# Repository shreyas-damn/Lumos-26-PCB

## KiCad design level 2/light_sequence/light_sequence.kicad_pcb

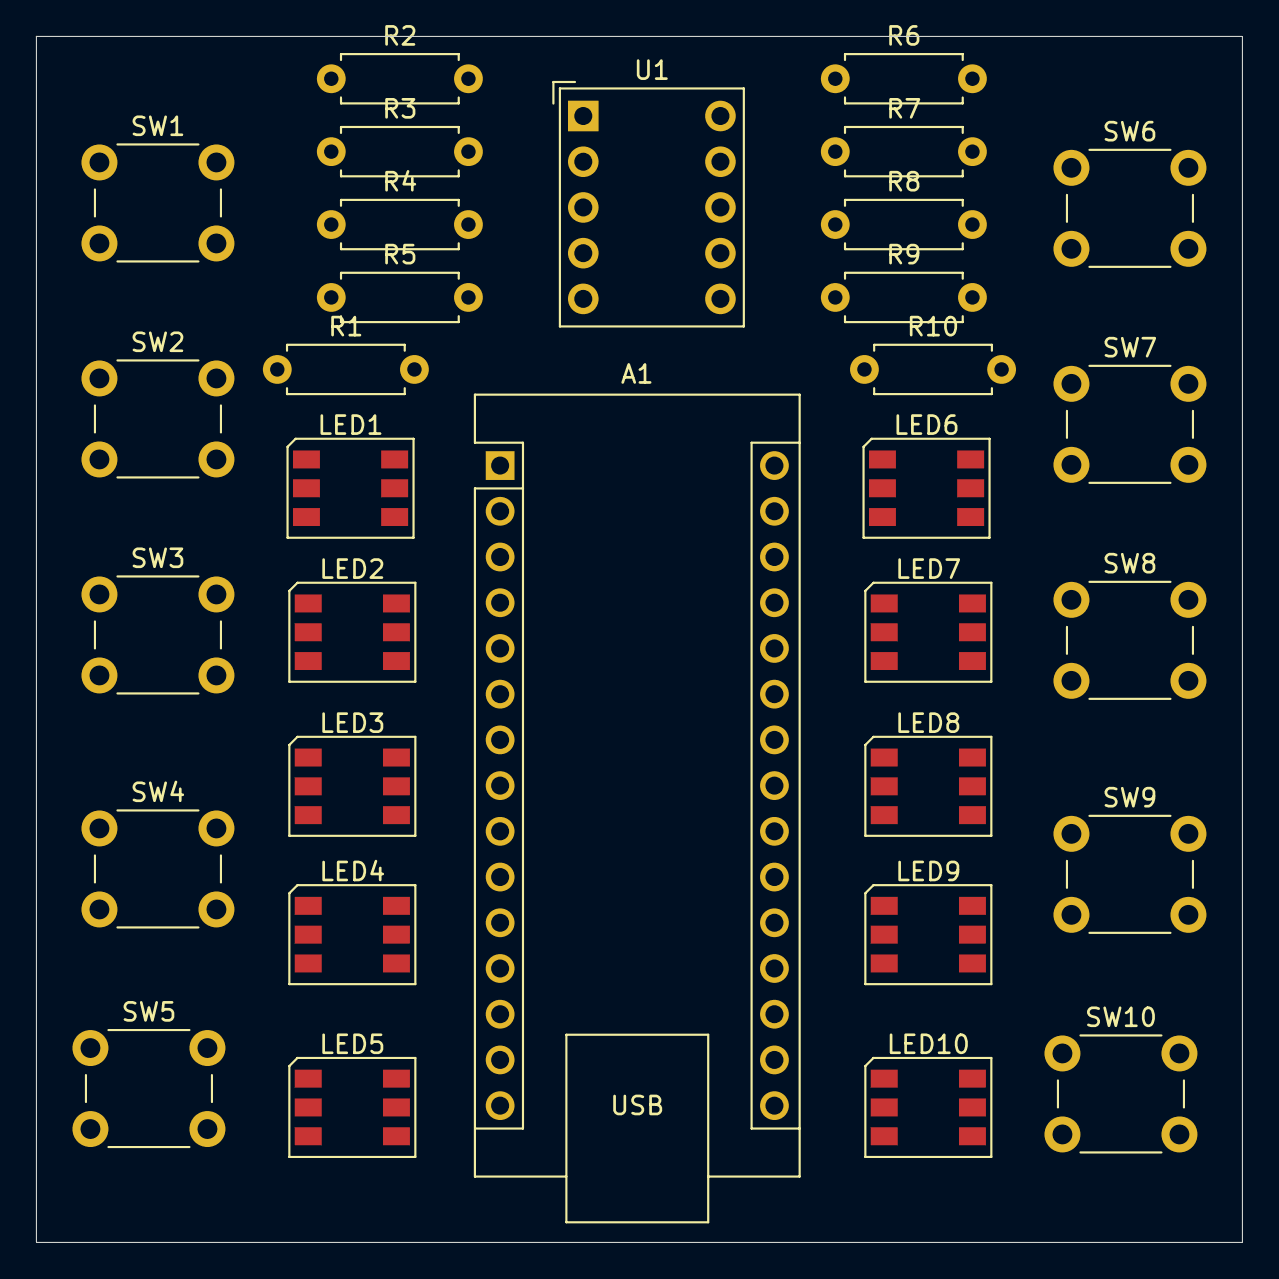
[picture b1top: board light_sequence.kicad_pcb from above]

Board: 2 copper layers, 67.0 x 67.0 mm, 32 parts (0 on the bottom side), 28 nets, no tracks yet.

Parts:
A1: Arduino_Nano_v3.x; Arduino_Nano
LED1, LED2, LED3, LED4, LED5, LED6, LED7, LED8, LED9, LED10: WS2812B; LED_WS2812_PLCC6_5.0x5.0mm_P1.6mm
R1, R10: 470; R_Axial_DIN0207_L6.3mm_D2.5mm_P7.62mm_Horizontal
R2, R3, R4, R5, R6, R7, R8, R9: 220; R_Axial_DIN0207_L6.3mm_D2.5mm_P7.62mm_Horizontal
SW1, SW2, SW3, SW4, SW5, SW6, SW7, SW8, SW9, SW10: SW_Push; SW_PUSH_6mm_H7.3mm
U1: SA39-11SRWA; Sx39-1xxxxx

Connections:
+5V: A1.27 (+5V), U1.3 (CA), U1.8 (CA)
GND: A1.4 (GND), SW1.1, SW2.2, SW3.2, SW4.2, SW5.2, SW6.2, SW7.2, SW8.2, SW9.2, SW10.2
unnamed: A1.19 (A0), SW2.1
unnamed: A1.20 (A1), SW3.1
unnamed: A1.21 (A2), SW4.1
unnamed: A1.22 (A3), SW5.1
unnamed: A1.23 (A4), SW6.1
unnamed: A1.24 (A5), SW7.1
unnamed: A1.25 (A6), SW8.1
unnamed: A1.26 (A7), SW9.1
unnamed: A1.6 (D3), SW10.1
unnamed: A1.8 (D5), SW1.2
unnamed: R2.2, U1.10 (A)
unnamed: R3.2, U1.9 (B)
unnamed: R4.2, U1.7 (C)
unnamed: R5.2, U1.5 (D)
unnamed: R6.2, U1.4 (E)
unnamed: R7.2, U1.2 (F)
unnamed: R8.2, U1.1 (G)
a: A1.10 (D7), R2.1
b: A1.11 (D8), R3.1
c: A1.12 (D9), R4.1
d: A1.13 (D10), R5.1
e: A1.14 (D11), R6.1
f: A1.15 (D12), R7.1
g: A1.16 (D13), R8.1
led_in: A1.9 (D6), R1.1
led_in2: A1.18 (AREF), R10.1

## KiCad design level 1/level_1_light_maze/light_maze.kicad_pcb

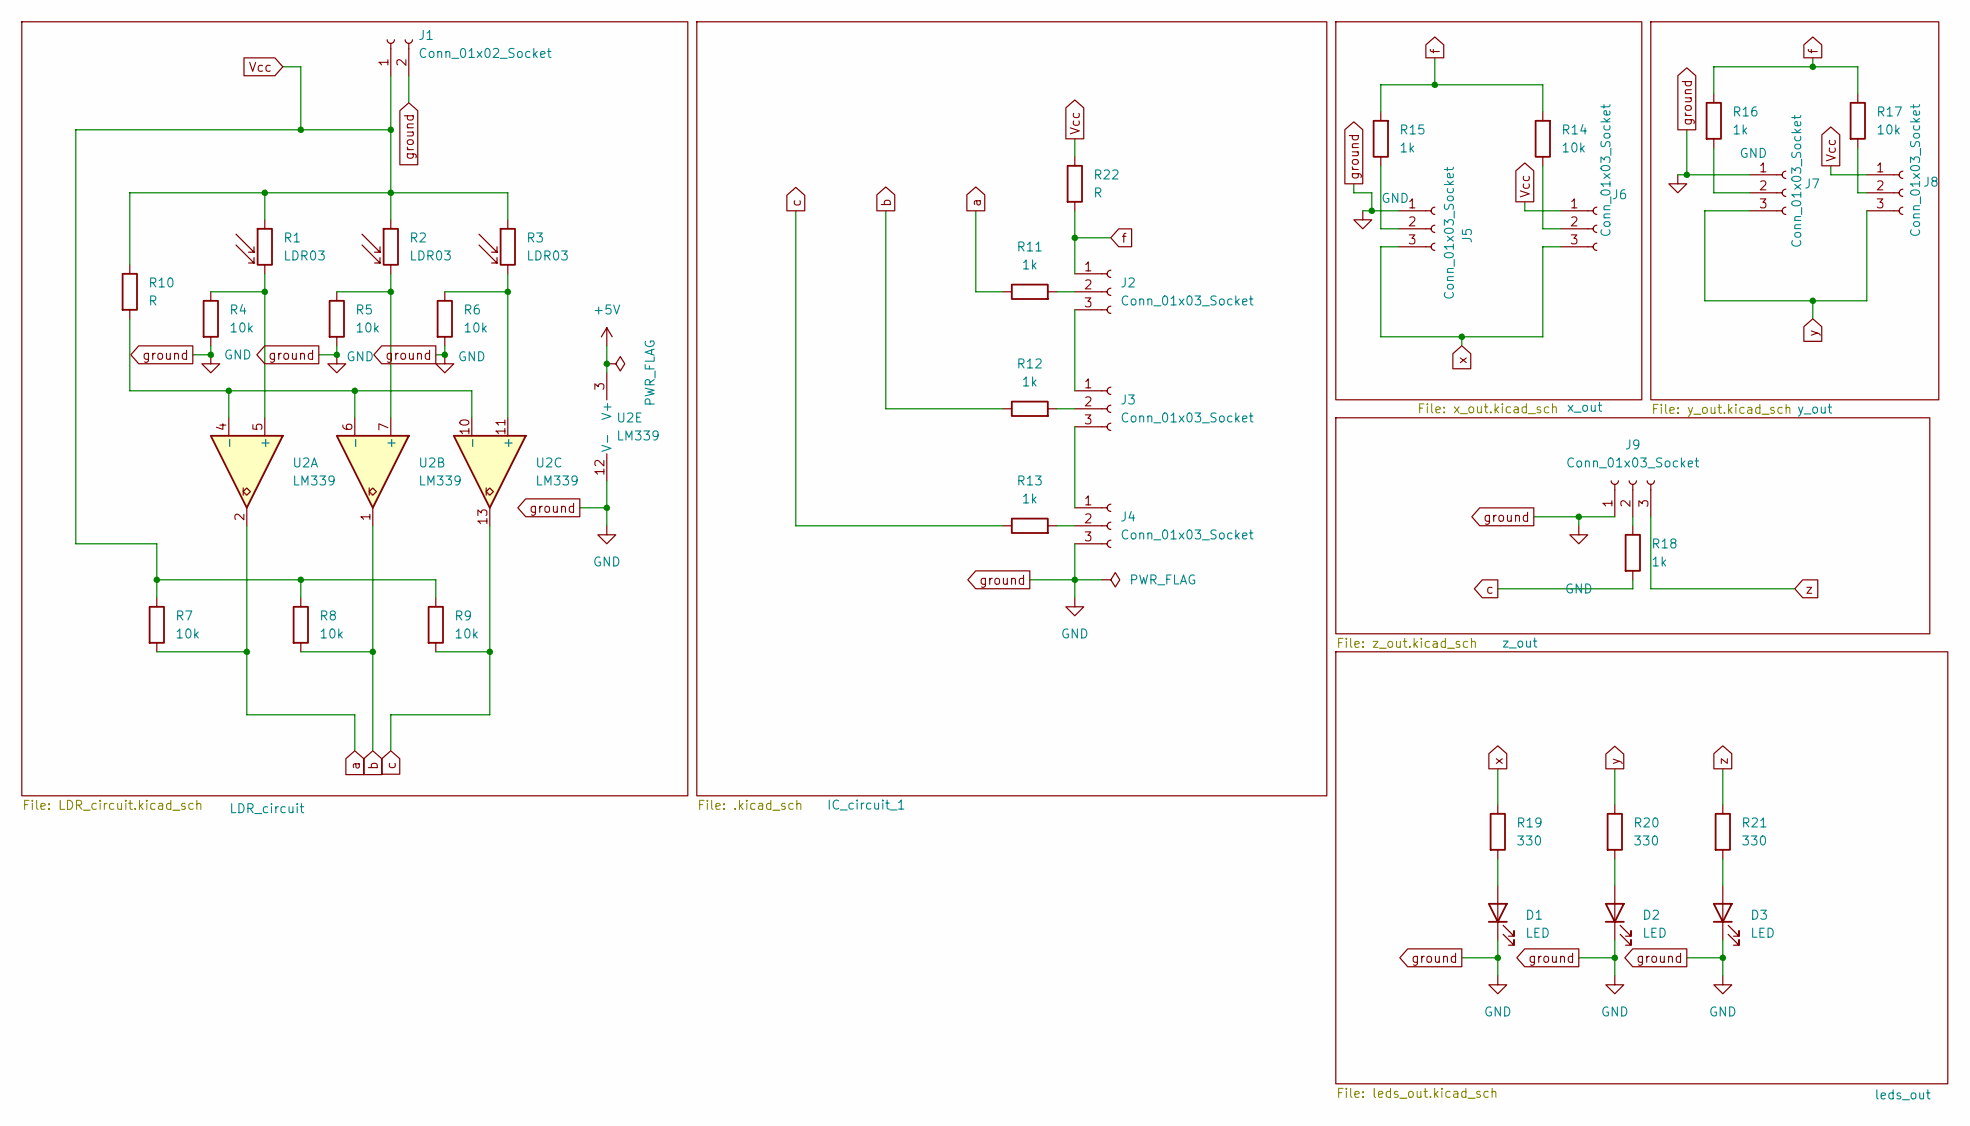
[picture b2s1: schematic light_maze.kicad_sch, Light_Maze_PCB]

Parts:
D1, D2, D3: LED; LED_D3.0mm_Horizontal_O1.27mm_Z2.0mm
J1: Conn_01x02_Socket; PinSocket_1x02_P2.54mm_Vertical
J2, J3, J4, J5, J6, J7, J8, J9: Conn_01x03_Socket; PinSocket_1x03_P2.54mm_Vertical
R1, R2, R3: LDR03; R_LDR_10x8.5mm_P7.6mm_Vertical
R4, R5, R6, R7, R8, R9, R14, R17: 10k; R_Axial_DIN0204_L3.6mm_D1.6mm_P5.08mm_Horizontal
R10, R22: R; R_Axial_DIN0204_L3.6mm_D1.6mm_P5.08mm_Horizontal
R11, R12, R13, R15, R16, R18: 1k; R_Axial_DIN0204_L3.6mm_D1.6mm_P5.08mm_Horizontal
R19, R20, R21: 330; R_Axial_DIN0204_L3.6mm_D1.6mm_P5.08mm_Horizontal
U2: LM339; SOIC-14_3.9x8.7mm_P1.27mm

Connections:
+5V: U2.3 (V+)
unnamed: D1.2 (A), R19.2
unnamed: D2.2 (A), R20.2
unnamed: D3.2 (A), R21.2
unnamed: J2.2, R11.2
unnamed: J2.3, J3.1
unnamed: J3.2, R12.2
unnamed: J3.3, J4.1
unnamed: J4.2, R13.2
unnamed: J5.2, R15.1
unnamed: J6.2, R14.1
unnamed: J7.2, R16.2
unnamed: J8.2, R17.2
unnamed: J9.2, R18.1
unnamed: R1.2, R4.1, U2.5 (+)
unnamed: R10.2, U2.4 (-), U2.6 (-), U2.10 (-)
unnamed: R2.2, R5.1, U2.7 (+)
unnamed: R3.2, R6.1, U2.11 (+)
Vcc: J1.1, J6.1, J8.1, R1.1, R2.1, R3.1, R7.1, R8.1, R9.1, R10.1, R22.1
a: R7.2, R11.1, U2.2
b: R8.2, R12.1, U2.1
c: R9.2, R13.1, R18.2, U2.13
f: J2.1, R14.2, R15.2, R16.1, R17.1, R22.2
ground: D1.1 (K), D2.1 (K), D3.1 (K), J1.2, J4.3, J5.1, J7.1, J9.1, R4.2, R5.2, R6.2, U2.12 (V-)
x: J5.3, J6.3, R19.1
y: J7.3, J8.3, R20.1
z: J9.3, R21.1

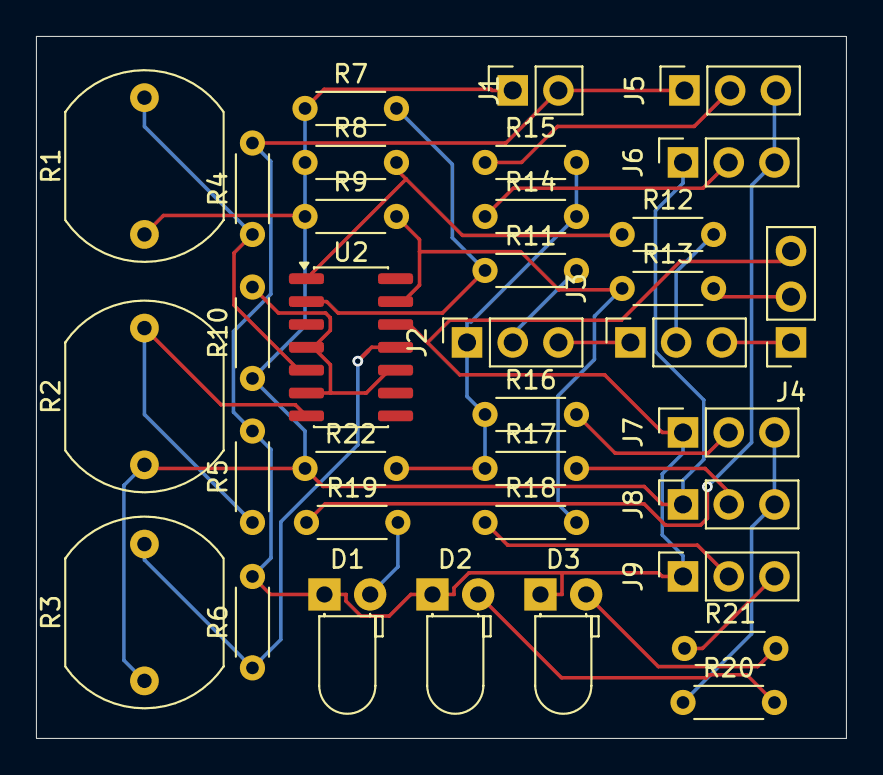
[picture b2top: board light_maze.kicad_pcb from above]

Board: 2 copper layers, 45.0 x 39.0 mm, 35 parts (0 on the bottom side), 26 nets.

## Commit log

2026-03-01 inital commit
2026-03-01 pcb changes
2026-03-01 pcb update
2026-03-01 light_maze_pcb_edit
2026-03-01 PCB routing
2026-03-01 light_seq_pcb layout
